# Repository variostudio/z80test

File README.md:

Simple schematics to blink LEDs with Zilog Z80 CPU

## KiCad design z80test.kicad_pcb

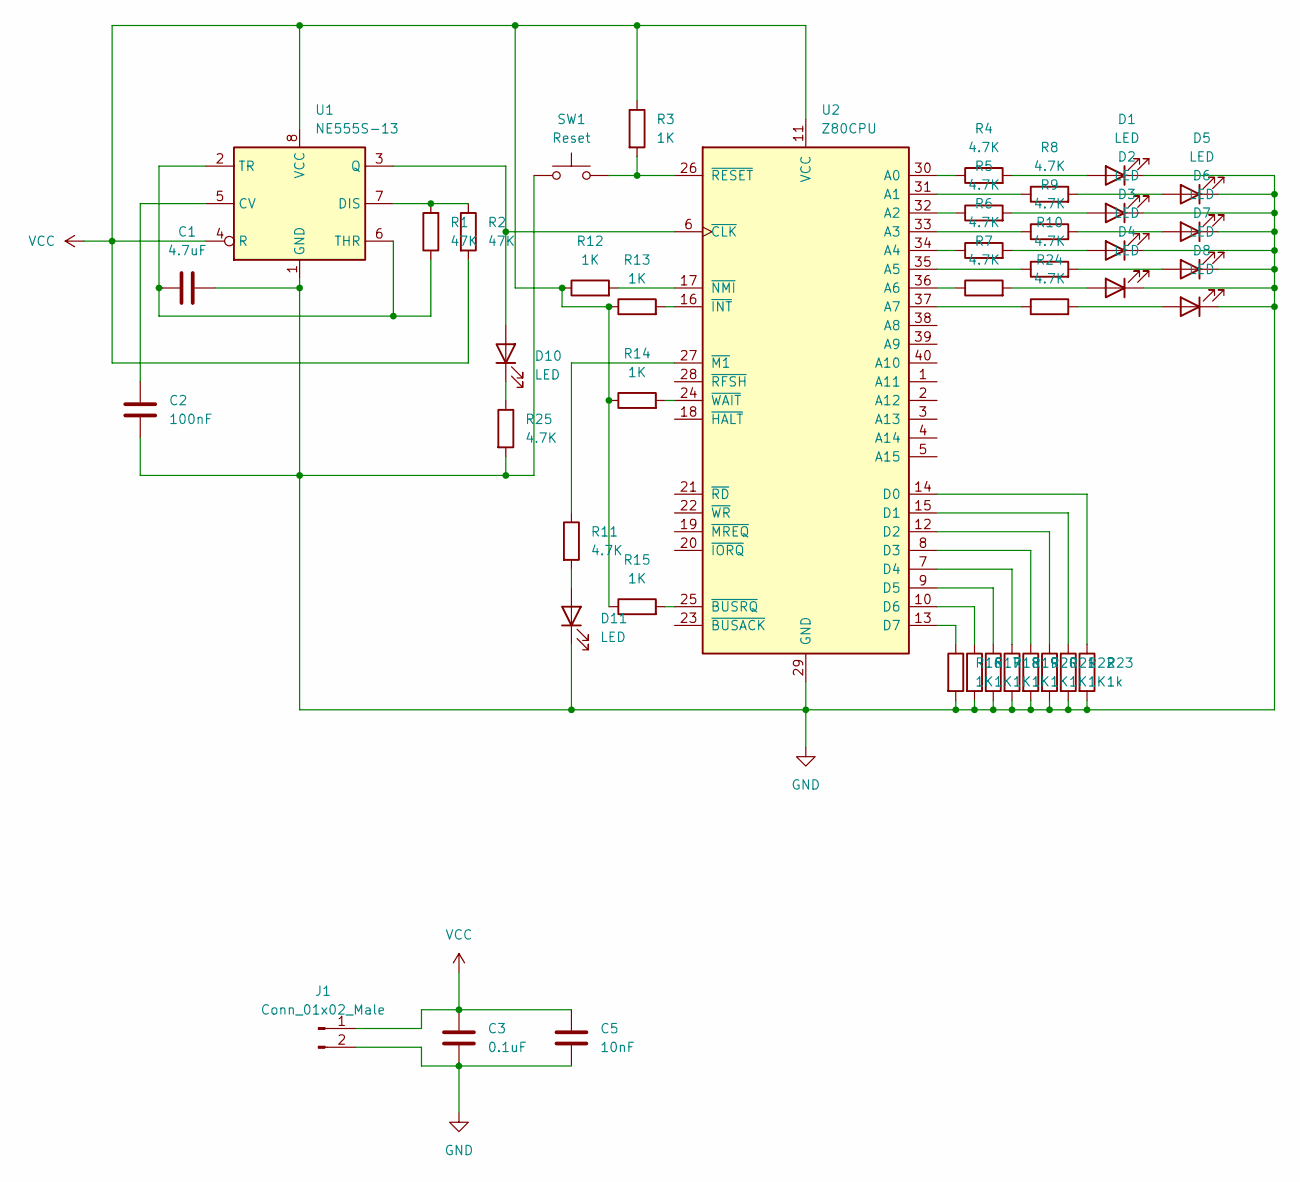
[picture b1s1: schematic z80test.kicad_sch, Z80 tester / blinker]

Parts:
C1: 4.7uF; C_0603_1608Metric
C2: 100nF; C_0603_1608Metric
C3: 0.1uF; C_0603_1608Metric
C5: 10nF; C_0603_1608Metric
D1, D2, D3, D4, D5, D6, D7, D8, D10, D11: LED; LED_0402_1005Metric
J1: Conn_01x02_Male; PinHeader_1x02_P2.54mm_Vertical
R1, R2: 47K; R_0603_1608Metric
R3, R12, R13, R14, R15, R16, R17, R18, R19, R20, R21, R22: 1K; R_0603_1608Metric
R4, R5, R6, R7, R8, R9, R10, R11, R24, R25: 4.7K; R_0603_1608Metric
R23: 1k; R_0603_1608Metric
SW1: Reset; SW_PUSH_6mm
U1: NE555S-13; SO-8_3.9x4.9mm_P1.27mm
U2: Z80CPU; DIP-40_W15.24mm_Socket

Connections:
GND: C1.2, C2.2, C3.2, C5.2, D1.1 (K), D2.1 (K), D3.1 (K), D4.1 (K), D5.1 (K), D6.1 (K), D7.1 (K), D8.1 (K), D11.1 (K), J1.2, R16.2, R17.2, R18.2, R19.2, R20.2, R21.2, R22.2, R23.2, R25.2, SW1.1, U1.1 (GND), U2.29 (GND)
unnamed: C1.1, R1.1, U1.2 (TR), U1.6 (THR)
unnamed: C2.1, U1.5 (CV)
unnamed: D1.2 (A), R4.2
unnamed: D2.2 (A), R5.2
unnamed: D3.2 (A), R6.2
unnamed: D4.2 (A), R7.2
unnamed: D5.2 (A), R8.2
unnamed: D6.2 (A), R9.2
unnamed: D7.2 (A), R10.2
unnamed: D8.2 (A), R24.2
unnamed: D10.1 (K), R25.1
unnamed: D10.2 (A), U1.3 (Q), U2.6 (~CLK)
unnamed: D11.2 (A), R11.2
unnamed: R1.2, R2.1, U1.7 (DIS)
unnamed: R3.2, SW1.2, U2.26 (~RESET)
unnamed: R4.1, U2.30 (A0)
unnamed: R5.1, U2.32 (A2)
unnamed: R6.1, U2.34 (A4)
unnamed: R7.1, U2.36 (A6)
unnamed: R8.1, U2.31 (A1)
unnamed: R9.1, U2.33 (A3)
unnamed: R10.1, U2.35 (A5)
unnamed: R11.1, U2.27 (~M1)
unnamed: R12.2, U2.17 (~NMI)
unnamed: R13.2, U2.16 (~INT)
unnamed: R14.2, U2.24 (~WAIT)
unnamed: R15.2, U2.25 (~BUSRQ)
unnamed: R16.1, U2.13 (D7)
unnamed: R17.1, U2.10 (D6)
unnamed: R18.1, U2.9 (D5)
unnamed: R19.1, U2.7 (D4)
unnamed: R20.1, U2.8 (D3)
unnamed: R21.1, U2.12 (D2)
unnamed: R22.1, U2.15 (D1)
unnamed: R23.1, U2.14 (D0)
unnamed: R24.1, U2.37 (A7)
VCC: C3.1, C5.1, J1.1, R2.2, R3.1, R12.1, R13.1, R14.1, R15.1, U1.4 (R), U1.8 (VCC), U2.11 (VCC)

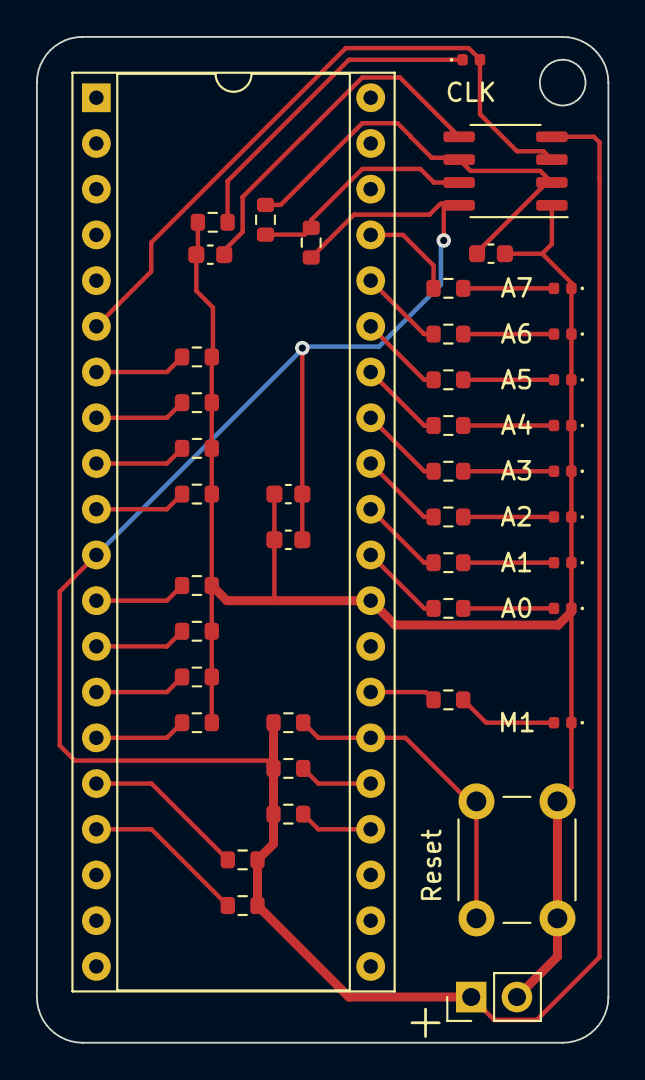
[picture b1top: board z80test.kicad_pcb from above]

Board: 2 copper layers, 31.8 x 55.9 mm, 43 parts (0 on the bottom side), 38 nets.

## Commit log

2022-11-22 Simple Z80 test circuit
